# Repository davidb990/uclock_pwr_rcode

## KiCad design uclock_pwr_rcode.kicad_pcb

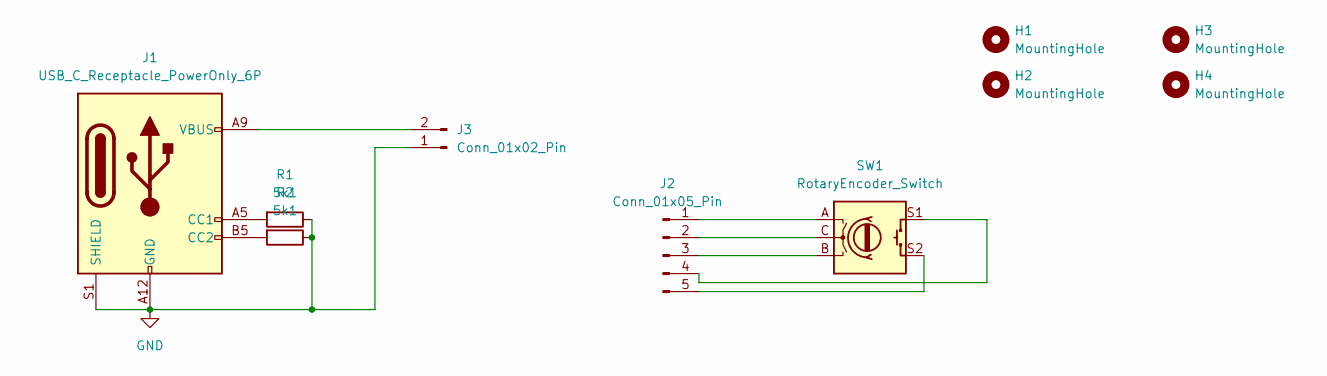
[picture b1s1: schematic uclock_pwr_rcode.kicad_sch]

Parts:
H1, H2, H3, H4: MountingHole; MountingHole_2.5mm
J1: USB_C_Receptacle_PowerOnly_6P; USB_C_Receptacle_GCT_USB4085
J2: Conn_01x05_Pin; PinHeader_1x05_P2.54mm_Vertical
J3: Conn_01x02_Pin; PinHeader_1x02_P2.54mm_Vertical
R1, R2: 5k1; R_0805_2012Metric
SW1: RotaryEncoder_Switch; RotaryEncoder_Bourns_Vertical_PEC12R-3x17F-Sxxxx

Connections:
GND: J1.A12 (GND), J1.B12 (GND), J1.S1 (SHIELD), J3.1, R1.1, R2.1
unnamed: J1.A5 (CC1), R1.2
unnamed: J1.B5 (CC2), R2.2
unnamed: J2.1, SW1.A
unnamed: J2.2, SW1.C
unnamed: J2.3, SW1.B
unnamed: J2.4, SW1.S1
unnamed: J2.5, SW1.S2
unnamed: J1.A9 (VBUS), J1.B9 (VBUS), J3.2

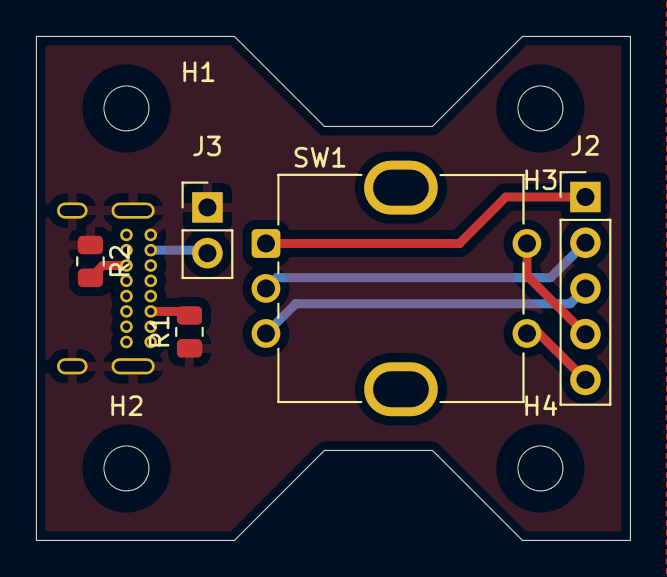
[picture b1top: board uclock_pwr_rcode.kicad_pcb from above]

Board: 2 copper layers, 33.0 x 28.0 mm, 10 parts (1 on the bottom side), 9 nets.

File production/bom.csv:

Designator,Footprint,Quantity,Value,LCSC Part #
J1,USB_C_Receptacle_GCT_USB4085,1,USB_C_Receptacle_PowerOnly_6P,
J2,PinHeader_1x05_P2.54mm_Vertical,1,Conn_01x05_Pin,
J3,PinHeader_1x02_P2.54mm_Vertical,1,Conn_01x02_Pin,
"R1, R2",0805,2,5k1,
SW1,RotaryEncoder_Bourns_Vertical_PEC12R-3x17F-Sxxxx,1,RotaryEncoder_Switch,

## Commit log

2025-09-30 init
2025-09-30 remove backups from git repo in prodction
2025-09-30 adding models
